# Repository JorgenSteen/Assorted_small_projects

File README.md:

# Assorted_small_projects
This repository contains projects which do not fit under a larger category and is too small to require its own repository.

Current content:
1. Led Matrix
2. Atmel Breakout board

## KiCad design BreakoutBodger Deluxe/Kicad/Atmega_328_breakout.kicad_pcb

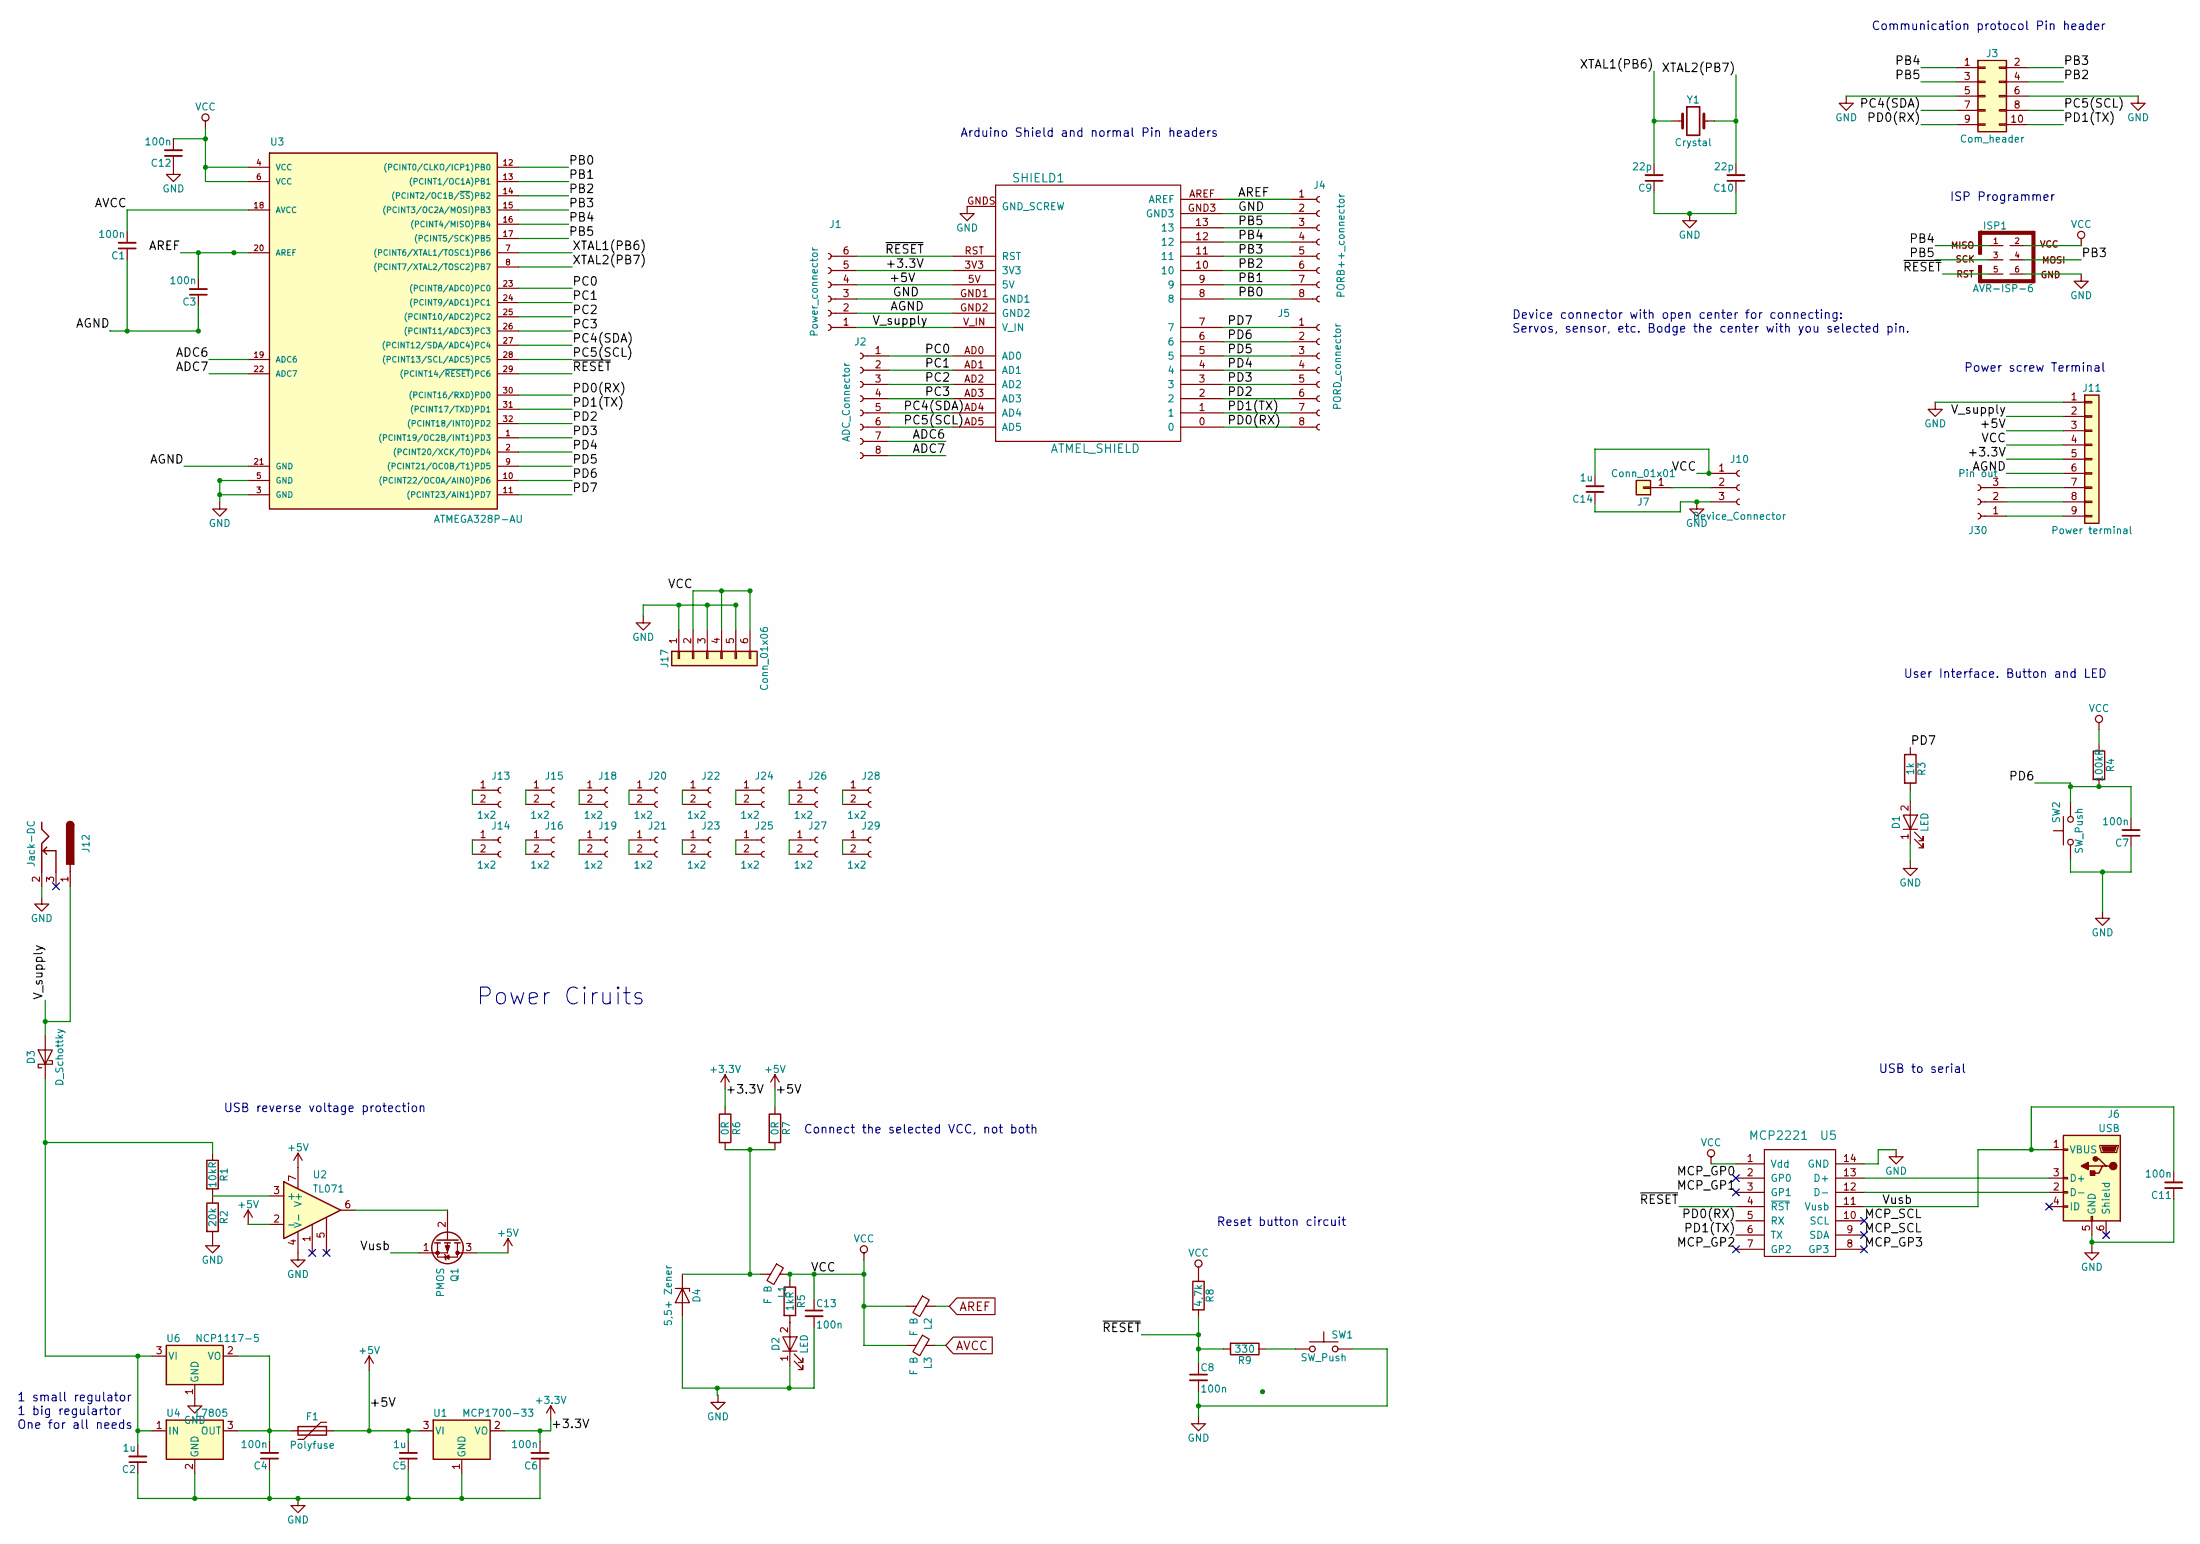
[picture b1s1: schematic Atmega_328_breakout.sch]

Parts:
C1, C3, C4, C6, C7, C8, C11, C12, C13: 100n; C_0603_HandSoldering
C2, C5, C14: 1u; C_0603_HandSoldering
C9, C10: 22p; C_0603_HandSoldering
D1, D2: LED; LED_0805_HandSoldering
D3: D_Schottky; D_A-405_P2.54mm_Vertical_KathodeUp
D4: 5,5+ Zener; D_0603
F1: Polyfuse
ISP1: AVR-ISP-6; Pin_Header_Straight_2x03_Pitch2.54mm
J1: Power_connector; Socket_Strip_Straight_1x06_Pitch2.54mm
J2: ADC_Connector; Socket_Strip_Straight_1x08_Pitch2.54mm
J3: Com_header; Pin_Header_Straight_2x05_Pitch2.54mm
J4: PORB++_connector; Socket_Strip_Straight_1x08_Pitch2.54mm
J5: PORD_connector; Socket_Strip_Straight_1x08_Pitch2.54mm
J6: USB; USB_Micro-B_Wuerth-629105150521
J7: Conn_01x01; Pin_Header_Straight_1x01_Pitch2.54mm
J10: Device_Connector; Pin_Header_Straight_1x03_Pitch2.54mm
J11: Power terminal; TerminalBlock_bornier-9_P5.08mm
J12: Jack-DC; JACK_ALIM
J13, J14, J15, J16, J18, J19, J20, J21, J22, J23, J24, J25, J26, J27, J28, J29: 1x2; Pin_Header_Straight_1x02_Pitch2.54mm
J17: Conn_01x06; Pin_Header_Straight_2x03_Pitch2.54mm
J30: Pin out; Pin_Header_Straight_1x03_Pitch2.54mm
L1, L2, L3: F B; L_0603_HandSoldering
Q1: PMOS; SOT-23
R1: 10kR; C_0603_HandSoldering
R2: 20k; C_0603_HandSoldering
R3: 1k; C_0603_HandSoldering
R4: 100kR; C_0603_HandSoldering
R5: 1kR; C_0603_HandSoldering
R6, R7: 0R; C_0603_HandSoldering
R8: 4,7k; C_0603_HandSoldering
R9: 330; C_0603_HandSoldering
SHIELD1: ATMEL_SHIELD; AtmelSHIELD
SW1, SW2: SW_Push; SW_PUSH_6mm_h5mm
U1: MCP1700-33; SOT-23
U2: TL071; SOIC-8-N
U3: ATMEGA328P-AU; TQFP-32_7x7mm_Pitch0.8mm
U4: L7805; TO-220
U5: MCP2221; SSOP-14
U6: NCP1117-5; SOT-23
Y1: Crystal; Crystal_HC49-U_Vertical

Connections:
+3V3: C6.2, J1.5, J11.5, R6.1, SHIELD1.3V3, U1.2 (VO)
+5V: C5.2, F1.1, J1.4, J11.3, Q1.3 (D), R7.1, SHIELD1.5V, U1.3 (VI), U2.2 (-), U2.7 (V+)
/ADC6: J2.7, U3.19 (ADC6)
/ADC7: J2.8, U3.22 (ADC7)
/AGND: C1.1, C3.1, J1.2, J11.6, SHIELD1.GND2, U3.21 (GND)
/MCP_GP0: U5.2 (GP0)
/MCP_GP1: U5.3 (GP1)
/MCP_GP2: U5.7 (GP2)
/MCP_GP3: U5.8 (GP3)
/MCP_SCL: U5.9 (SDA), U5.10 (SCL)
/PB0: J4.8, SHIELD1.8, U3.12 ((PCINT0/CLKO/ICP1)PB0)
/PB1: J4.7, SHIELD1.9, U3.13 ((PCINT1/OC1A)PB1)
/PB2: J3.4, J4.6, SHIELD1.10, U3.14 ((PCINT2/OC1B/~SS~)PB2)
/PB3: ISP1.4, J3.2, J4.5, SHIELD1.11, U3.15 ((PCINT3/OC2A/MOSI)PB3)
/PB4: ISP1.1, J3.1, J4.4, SHIELD1.12, U3.16 ((PCINT4/MISO)PB4)
/PB5: ISP1.3, J3.3, J4.3, SHIELD1.13, U3.17 ((PCINT5/SCK)PB5)
/PC0: J2.1, SHIELD1.AD0, U3.23 ((PCINT8/ADC0)PC0)
/PC1: J2.2, SHIELD1.AD1, U3.24 ((PCINT9/ADC1)PC1)
/PC2: J2.3, SHIELD1.AD2, U3.25 ((PCINT10/ADC2)PC2)
/PC3: J2.4, SHIELD1.AD3, U3.26 ((PCINT11/ADC3)PC3)
/PC4(SDA): J2.5, J3.7, SHIELD1.AD4, U3.27 ((PCINT12/SDA/ADC4)PC4)
/PC5(SCL): J2.6, J3.8, SHIELD1.AD5, U3.28 ((PCINT13/SCL/ADC5)PC5)
/PD0(RX): J3.9, J5.8, SHIELD1.0, U3.30 ((PCINT16/RXD)PD0), U5.5 (RX)
/PD1(TX): J3.10, J5.7, SHIELD1.1, U3.31 ((PCINT17/TXD)PD1), U5.6 (TX)
/PD2: J5.6, SHIELD1.2, U3.32 ((PCINT18/INT0)PD2)
/PD3: J5.5, SHIELD1.3, U3.1 ((PCINT19/OC2B/INT1)PD3)
/PD4: J5.4, SHIELD1.4, U3.2 ((PCINT20/XCK/T0)PD4)
/PD5: J5.3, SHIELD1.5, U3.9 ((PCINT21/OC0B/T1)PD5)
/PD6: C7.2, J5.2, R4.2, SHIELD1.6, SW2.2, U3.10 ((PCINT22/OC0A/AIN0)PD6)
/PD7: J5.1, R3.1, SHIELD1.7, U3.11 ((PCINT23/AIN1)PD7)
/V_supply: D3.2 (A), J1.1, J11.2, J12.1, SHIELD1.V_IN
/Vusb: C11.2, J6.1 (VBUS), Q1.1 (S), U5.11 (Vusb)
/XTAL1(PB6): C9.2, U3.7 ((PCINT6/XTAL1/TOSC1)PB6), Y1.1
/XTAL2(PB7): C10.2, U3.8 ((PCINT7/XTAL2/TOSC2)PB7), Y1.2
/~RESET: C8.1, ISP1.5, J1.6, R8.2, R9.2, SHIELD1.RST, U3.29 ((PCINT14/~RESET~)PC6), U5.4 (~RST)
AREF: C3.2, J4.1, L2.1, SHIELD1.AREF, U3.20 (AREF)
AVCC: C1.2, L3.1, U3.18 (AVCC)
GND: C2.1, C4.1, C5.1, C6.1, C7.1, C8.2, C9.1, C10.1, C11.1, C12.1, C13.2, C14.1, D1.1 (K), D2.1 (K), D4.2 (A), ISP1.6, J1.3, J3.5, J3.6, J4.2, J6.5 (GND), J10.3, J11.1, J12.2, J17.1, J17.3, J17.5, R2.2, SHIELD1.GND1, SHIELD1.GND3, SHIELD1.GNDS (GND_SCREW), SW1.2, SW2.1, U1.1 (GND), U2.4 (V-), U3.3 (GND), U3.5 (GND), U4.2 (GND), U5.14 (GND), U6.1 (GND); also elsewhere on the board
unnamed: C2.2, D3.1 (K), R1.1, U4.1 (IN), U6.3 (VI)
unnamed: C4.2, F1.2, U4.3 (OUT), U6.2 (VO)
unnamed: D1.2 (A), R3.2
unnamed: D2.2 (A), R5.2
unnamed: D4.1 (K), L1.2, R6.2, R7.2
unnamed: J6.2 (D-), U5.12 (D-)
unnamed: J6.3 (D+), U5.13 (D+)
unnamed: J7.1, J10.2
unnamed: J11.7, J30.3
unnamed: J11.8, J30.2
unnamed: J11.9, J30.1
unnamed: J13.1, J13.2
unnamed: J14.1, J14.2
unnamed: J15.1, J15.2
unnamed: J16.1, J16.2
unnamed: J18.1, J18.2
unnamed: J19.1, J19.2
unnamed: J20.1, J20.2
unnamed: J21.1, J21.2
unnamed: J22.1, J22.2
unnamed: J23.1, J23.2
unnamed: J24.1, J24.2
unnamed: J25.1, J25.2
unnamed: J26.1, J26.2
unnamed: J27.1, J27.2
unnamed: J28.1, J28.2
unnamed: J29.1, J29.2
unnamed: Q1.2 (G), U2.6
unnamed: R1.2, R2.1, U2.3 (+)
unnamed: R9.1, SW1.1
VCC: C12.2, C13.1, C14.2, ISP1.2, J10.1, J11.4, J17.2, J17.4, J17.6, L1.1, L2.2, L3.2, R4.1, R5.1, R8.1, U3.4 (VCC), U3.6 (VCC), U5.1 (Vdd)

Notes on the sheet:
User Interface. Button and LED
Power screw Terminal
ISP Programmer
Communication protocol Pin header
Device connector with open center for connecting: Servos, sensor, etc. Bodge the center with you selected pin.
USB to serial
Reset button circuit
Power Ciruits
Arduino Shield and normal Pin headers
USB reverse voltage protection
1 small regulator 1 big regulartor One for all needs
Connect the selected VCC, not both

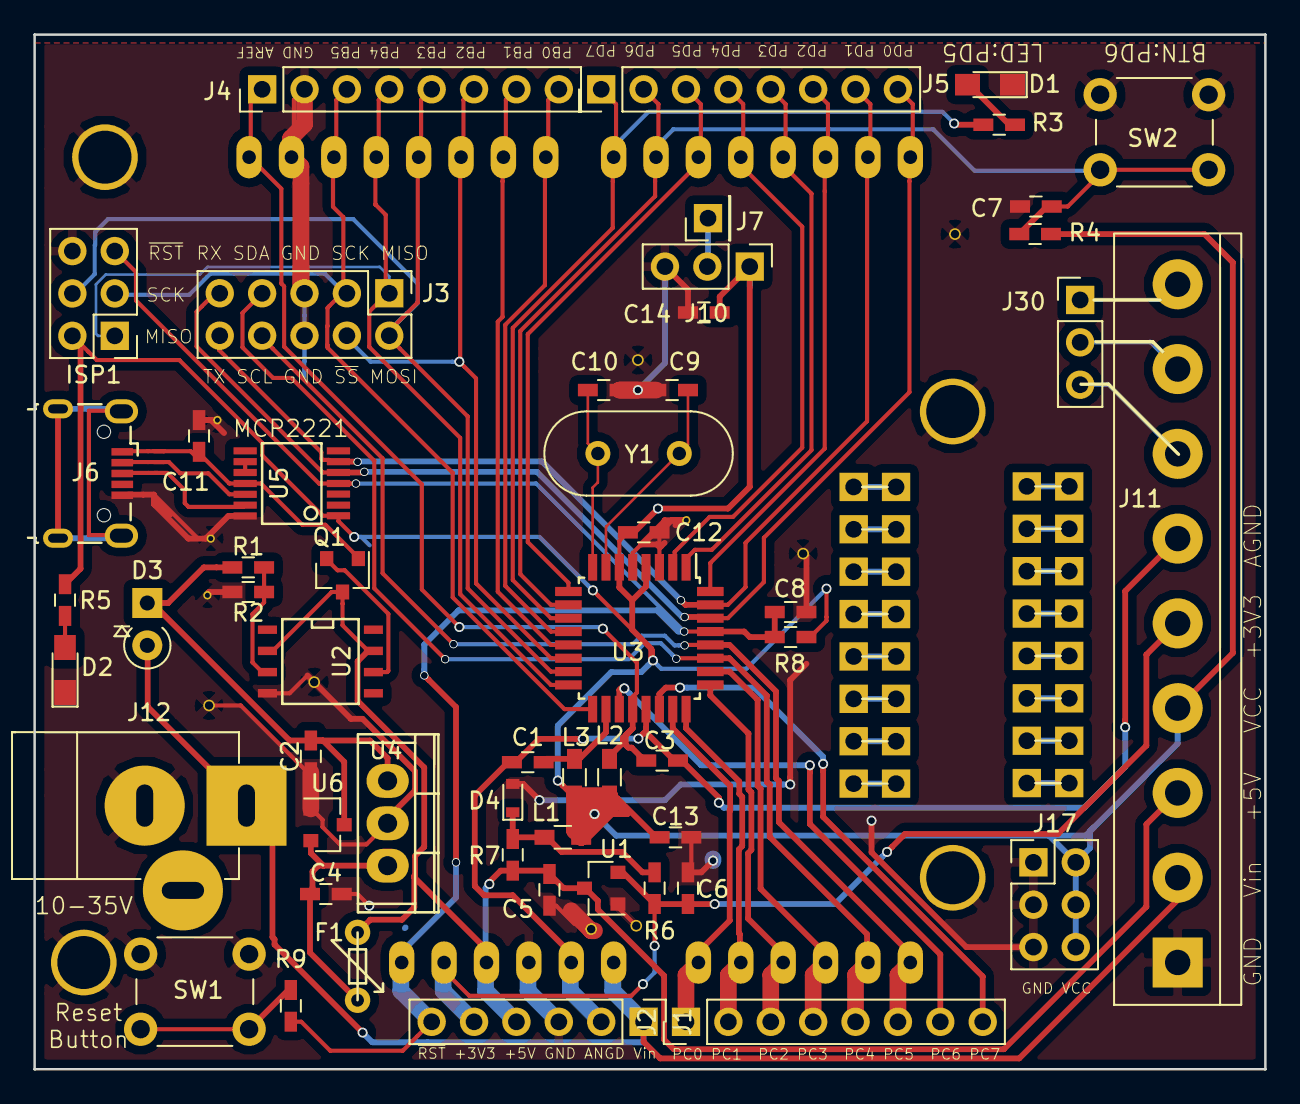
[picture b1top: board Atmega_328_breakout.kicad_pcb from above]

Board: 2 copper layers, 73.8 x 62.0 mm, 80 parts (0 on the bottom side), 65 nets.

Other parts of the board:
GND: VIA_GND; VIA_GND_0,5
GND#2, GND#3, GND#4, GND#7, GND#9: VIA_GND; VIA_GND_0,5
GND#5, GND#6, GND#8: VIA_GND; VIA_GND_0,3

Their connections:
GND: GND.GND, GND#2.GND, GND#3.GND, GND#4.GND, GND#5.GND, GND#6.GND, GND#7.GND, GND#8.GND, GND#9.GND; also elsewhere on the board

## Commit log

2017-12-21 Added some information.
2017-12-21 3D models in .skp and stl
    Remember that the base must be an opaque material for the LED's light to be defused. If you print with a see through material, it will likely become opaque in the printing process.
2017-12-21 Added info about 3D-material.
2017-12-21 Added info
2018-01-26 Fixed universal size matrix
2018-01-26 name edit
2018-01-27 With sharp corners
2018-02-06 Breakoutbodger
2018-02-06 morefile
2018-02-07 The Kicad file
2018-02-07 Parts
2018-02-07 Picture and increase in trace size
2018-02-09 Fixed readme
2018-02-09 test
2018-02-09 compensate for 3d-print fault
2018-02-15 TODOlist
2018-02-15 Added for not perfekt print
2018-02-15 todo
2018-02-19 Sorted
2018-02-19 Sorted folders
2018-02-19 sorting
2018-02-19 Folder fixing
2018-02-20 new stl
2018-02-25 Fixed edge and added MCU box
2018-02-25 edit top
2018-02-26 Lagde stl
2020-09-26 added metal detector
